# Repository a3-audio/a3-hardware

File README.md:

# SPDX-FileCopyrightText: 2017 Free Software Foundation Europe e.V. <https://fsfe.org>
#
# SPDX-License-Identifier: CERN-OHL-S-2.0

Copyright A3 Audio UG (haftungsbeschränkt) 2022.

This source describes Open Hardware and is licensed under the
CERN-OHL-S v2. You may redistribute and modify this source and make
products using it under the terms of the CERN-OHL-S v2
(https://cern-ohl.web.cern.ch).

This source is distributed WITHOUT ANY EXPRESS OR IMPLIED WARRANTY,
INCLUDING OF MERCHANTABILITY, SATISFACTORY QUALITY AND FITNESS FOR A
PARTICULAR PURPOSE. Please see the CERN-OHL-S v2 for applicable
conditions.

Source location: https://github.com/a3-audio/a3-hardware

As per CERN-OHL-S v2 section 4, should You produce hardware based on
this source, You must where practicable maintain the Source Location
visible on the external case of all products you
make using this source.

You may use "reuse" to check license validation:
https://reuse.readthedocs.io/en/stable/readme.html

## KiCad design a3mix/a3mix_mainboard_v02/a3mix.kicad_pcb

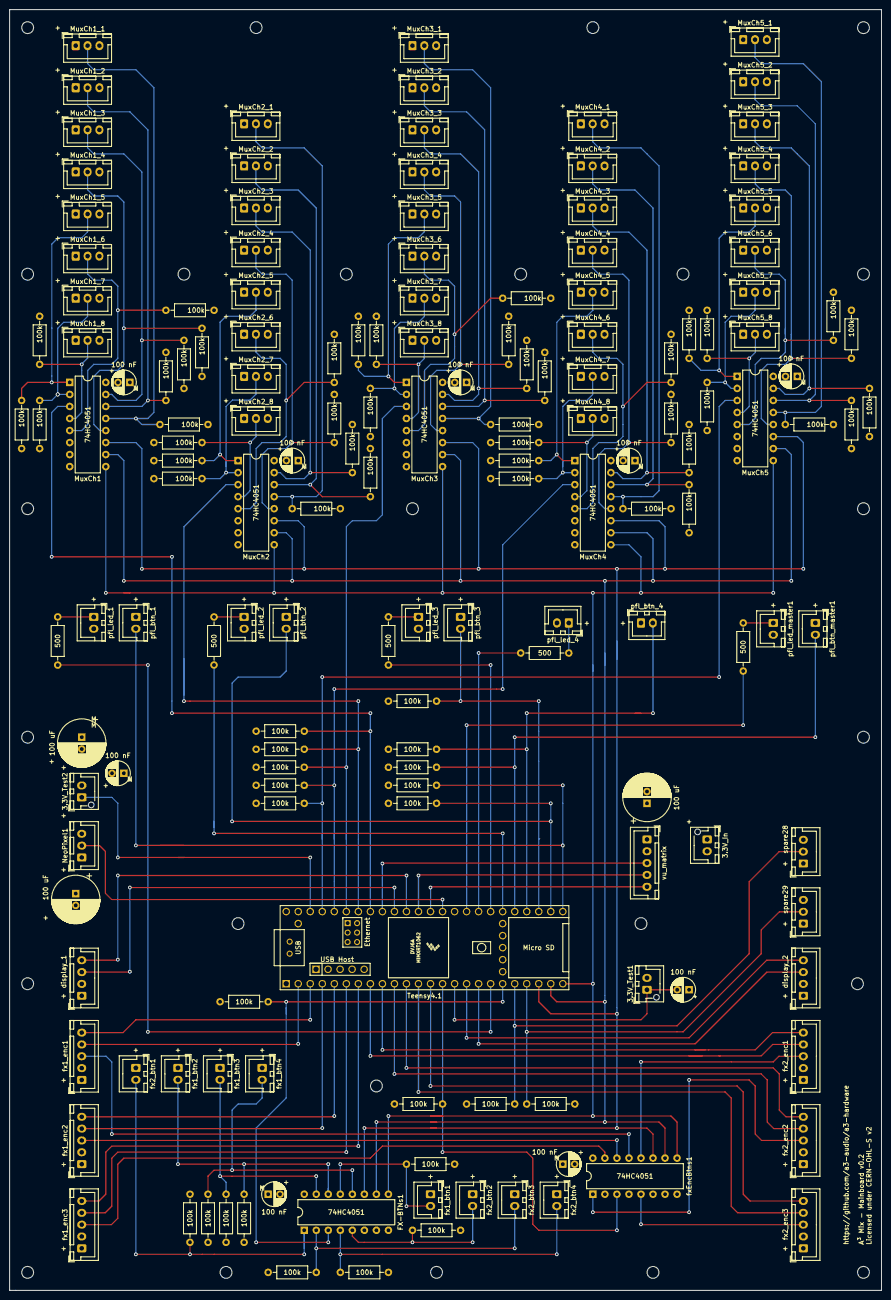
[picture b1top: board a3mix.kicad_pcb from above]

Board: 4 copper layers, 184.2 x 270.5 mm, 160 parts (0 on the bottom side), 105 nets.

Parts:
3.3V_In, 3.3V_Test1, 3.3V_Test2: Conn_01x02; JST_XH_B2B-XH-AM_1x02_P2.50mm_Vertical
C1, C2, C7: 100 uF; CP_Radial_D10.0mm_P2.50mm
C3, C4, C5, C6, C8, C9, C10, C11, C12: 100 nF; CP_Radial_D5.0mm_P2.50mm
FX-BTNs1: 74HC4051; DIP-16_W7.62mm
MuxCh1, MuxCh2, MuxCh3, MuxCh4, MuxCh5: 74HC4051; DIP-16_W7.62mm
MuxCh1_1, MuxCh1_2, MuxCh1_3, MuxCh1_4, MuxCh1_5, MuxCh1_6, MuxCh1_7, MuxCh1_8, MuxCh2_1, MuxCh2_2, MuxCh2_3, MuxCh2_4, MuxCh2_5, MuxCh2_6, MuxCh2_7, MuxCh2_8, MuxCh3_1, MuxCh3_2, MuxCh3_3, MuxCh3_4, MuxCh3_5, MuxCh3_6, MuxCh3_7, MuxCh3_8, MuxCh4_1, MuxCh4_2, MuxCh4_3, MuxCh4_4, MuxCh4_5, MuxCh4_6, MuxCh4_7, MuxCh4_8, MuxCh5_1, MuxCh5_2, MuxCh5_3, MuxCh5_4, MuxCh5_5, MuxCh5_6, MuxCh5_7, MuxCh5_8: Conn_01x03; JST_XH_B3B-XH-A_1x03_P2.50mm_Vertical
NeoPixel1: Conn_01x03; JST_XH_B3B-XH-A_1x03_P2.50mm_Vertical
R1, R2, R3, R4, R5, R6, R7, R8, R9, R10, R11, R12, R13, R14, R15, R16, R17, R19, R20, R21, R22, R23, R24, R25, R26, R27, R28, R29, R34, R35, R36, R37, R38, R39, R40, R41, R42, R43, R44, R45, R46, R47, R48, R49, R50, R51, R52, R53, R54, R55, R56, R57, R58, R59, R60, R61, R62, R63, R64, R65, R66, R67: 100k; R_Axial_DIN0207_L6.3mm_D2.5mm_P10.16mm_Horizontal
R18, R30, R31, R32, R33: 500; R_Axial_DIN0207_L6.3mm_D2.5mm_P10.16mm_Horizontal
U5: Teensy4.1; Teensy41
display_1, display_2: Conn_01x04; JST_XH_B4B-XH-A_1x04_P2.50mm_Vertical
fx1_btn1, fx1_btn2, fx1_btn3, fx1_btn4, fx2_btn1, fx2_btn2, fx2_btn3, fx2_btn4: Conn_01x02; JST_XH_B2B-XH-A_1x02_P2.50mm_Vertical
fx1_enc1, fx1_enc2, fx1_enc3, fx2_enc1, fx2_enc2, fx2_enc3: Conn_01x05; JST_XH_B5B-XH-A_1x05_P2.50mm_Vertical
fxEncBtns1: 74HC4051; DIP-16_W7.62mm
pfl_btn_1, pfl_btn_2, pfl_btn_3, pfl_btn_4: Conn_01x02; JST_XH_B2B-XH-A_1x02_P2.50mm_Vertical
pfl_btn_master1: Conn_01x02; JST_XH_B2B-XH-A_1x02_P2.50mm_Vertical
pfl_led_1, pfl_led_2, pfl_led_3, pfl_led_4: Conn_01x02; JST_XH_B2B-XH-A_1x02_P2.50mm_Vertical
pfl_led_master1: Conn_01x02; JST_XH_B2B-XH-A_1x02_P2.50mm_Vertical
spare28, spare29: Conn_01x03; JST_XH_B3B-XH-A_1x03_P2.50mm_Vertical
vu_matrix: MAX7219 led matrix vu; JST_XH_B5B-XH-A_1x05_P2.50mm_Vertical

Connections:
+3V3: 3.3V_In.1, 3.3V_Test1.2, 3.3V_Test2.2, C1.1, C2.1, C4.2, C5.2, C6.2, C7.2, C8.2, C9.2, C10.2, C11.2, C12.2, FX-BTNs1.16, MuxCh1.16, MuxCh1_1.1, MuxCh1_2.1, MuxCh1_3.1, MuxCh1_4.1, MuxCh1_5.1, MuxCh1_6.1, MuxCh1_7.1, MuxCh1_8.1, MuxCh2.16, MuxCh2_1.1, MuxCh2_2.1, MuxCh2_3.1, MuxCh2_4.1, MuxCh2_5.1, MuxCh2_6.1, MuxCh2_7.1, MuxCh2_8.1, MuxCh3.16, MuxCh3_1.1, MuxCh3_2.1, MuxCh3_3.1, MuxCh3_4.1, MuxCh3_5.1, MuxCh3_6.1, MuxCh3_7.1, MuxCh3_8.1, MuxCh4.16, MuxCh4_1.1, MuxCh4_2.1, MuxCh4_3.1, MuxCh4_4.1, MuxCh4_5.1, MuxCh4_6.1, MuxCh4_7.1, MuxCh4_8.1, MuxCh5.16, MuxCh5_1.1, MuxCh5_2.1, MuxCh5_3.1, MuxCh5_4.1, MuxCh5_5.1, MuxCh5_6.1, MuxCh5_7.1, MuxCh5_8.1, NeoPixel1.1, display_1.1, display_2.1, fx1_btn1.1, fx1_btn2.1, fx1_btn3.1, fx1_btn4.1, fx1_enc1.1, fx1_enc2.1, fx1_enc3.1, fx2_btn1.1, fx2_btn2.1, fx2_btn3.1, fx2_btn4.1, fx2_enc1.1, fx2_enc2.1, fx2_enc3.1, fxEncBtns1.16, pfl_btn_1.1, pfl_btn_2.1, pfl_btn_3.1, pfl_btn_4.1, pfl_btn_master1.1, spare28.1, spare29.1, vu_matrix.1
GND: 3.3V_In.2, C1.2, C2.2, C3.1, C4.1, C5.1, C6.1, C7.1, C8.1, C9.1, C10.1, C11.1, C12.1, FX-BTNs1.6, FX-BTNs1.7, FX-BTNs1.8, MuxCh1.6, MuxCh1.7, MuxCh1.8, MuxCh1_1.3, MuxCh1_2.3, MuxCh1_3.3, MuxCh1_4.3, MuxCh1_5.3, MuxCh1_6.3, MuxCh1_7.3, MuxCh1_8.3, MuxCh2.6, MuxCh2.7, MuxCh2.8, MuxCh2_1.3, MuxCh2_2.3, MuxCh2_3.3, MuxCh2_4.3, MuxCh2_5.3, MuxCh2_6.3, MuxCh2_7.3, MuxCh2_8.3, MuxCh3.6, MuxCh3.7, MuxCh3.8, MuxCh3_1.3, MuxCh3_2.3, MuxCh3_3.3, MuxCh3_4.3, MuxCh3_5.3, MuxCh3_6.3, MuxCh3_7.3, MuxCh3_8.3, MuxCh4.6, MuxCh4.7, MuxCh4.8, MuxCh4_1.3, MuxCh4_2.3, MuxCh4_3.3, MuxCh4_4.3, MuxCh4_5.3, MuxCh4_6.3, MuxCh4_7.3, MuxCh4_8.3, MuxCh5.6, MuxCh5.7, MuxCh5.8, MuxCh5_1.3, MuxCh5_2.3, MuxCh5_3.3, MuxCh5_4.3, MuxCh5_5.3, MuxCh5_6.3, MuxCh5_7.3, MuxCh5_8.3, NeoPixel1.3, R1.2, R2.2, R3.2, R4.2, R5.2, R6.2, R7.2, R8.2, R9.2, R10.2, R11.2, R12.2, R13.2, R14.2, R15.2, R16.2, R17.2, R19.2, R20.2, R21.2, R22.2, R23.2, R24.2, R25.2, R26.2, R27.2, R28.2, R29.2, R34.2, R35.2, R36.2, R37.2, R38.2, R39.2, R40.2, R41.2, R42.2, R43.2, R44.2, R45.2, R46.2, R47.2, R48.2, R49.2, R50.2, R51.2, R52.2, R53.2, R54.2, R55.2, R56.2, R57.2, R58.2, R59.2, R60.2, R61.2, R62.2, R63.2, R64.2, R65.2, R66.2, R67.2, U5.1, U5.34, U5.47, display_1.2, display_2.2, fx1_enc1.2, fx1_enc2.2, fx1_enc3.2, fx2_enc1.2, fx2_enc2.2, fx2_enc3.2, fxEncBtns1.6, fxEncBtns1.7, fxEncBtns1.8, pfl_led_1.2, pfl_led_2.2, pfl_led_3.2, pfl_led_4.2, pfl_led_master1.2, spare28.3, spare29.3, vu_matrix.2
unnamed: 3.3V_Test1.1, C3.2, U5.15
unnamed: 3.3V_Test2.1, U5.46
unnamed: FX-BTNs1.1, R5.1, fx2_btn1.2
unnamed: FX-BTNs1.2, R7.1, fx2_btn3.2
unnamed: FX-BTNs1.4, R8.1, fx2_btn4.2
unnamed: FX-BTNs1.5, R6.1, fx2_btn2.2
unnamed: FX-BTNs1.12, R4.1, fx1_btn4.2
unnamed: FX-BTNs1.13, R1.1, fx1_btn1.2
unnamed: FX-BTNs1.14, R2.1, fx1_btn2.2
unnamed: FX-BTNs1.15, R3.1, fx1_btn3.2
unnamed: MuxCh1.1, MuxCh1_5.2, R13.1
unnamed: MuxCh1.2, MuxCh1_7.2, R15.1
unnamed: MuxCh1.4, MuxCh1_8.2, R16.1
unnamed: MuxCh1.5, MuxCh1_6.2, R14.1
unnamed: MuxCh1.12, MuxCh1_4.2, R12.1
unnamed: MuxCh1.13, MuxCh1_1.2, R9.1
unnamed: MuxCh1.14, MuxCh1_2.2, R10.1
unnamed: MuxCh1.15, MuxCh1_3.2, R11.1
unnamed: MuxCh2.13, MuxCh2_1.2, R22.1
unnamed: MuxCh2.14, MuxCh2_2.2, R23.1
unnamed: MuxCh2.15, MuxCh2_3.2, R24.1
unnamed: MuxCh2.12, MuxCh2_4.2, R25.1
unnamed: MuxCh2.1, MuxCh2_5.2, R26.1
unnamed: MuxCh2.5, MuxCh2_6.2, R27.1
unnamed: MuxCh2.2, MuxCh2_7.2, R28.1
unnamed: MuxCh2.4, MuxCh2_8.2, R29.1
unnamed: MuxCh3.13, MuxCh3_1.2, R44.1
unnamed: MuxCh3.14, MuxCh3_2.2, R45.1
unnamed: MuxCh3.15, MuxCh3_3.2, R46.1
unnamed: MuxCh3.12, MuxCh3_4.2, R47.1
unnamed: MuxCh3.1, MuxCh3_5.2, R48.1
unnamed: MuxCh3.5, MuxCh3_6.2, R49.1
unnamed: MuxCh3.2, MuxCh3_7.2, R50.1
unnamed: MuxCh3.4, MuxCh3_8.2, R51.1
unnamed: MuxCh4.13, MuxCh4_1.2, R52.1
unnamed: MuxCh4.14, MuxCh4_2.2, R53.1
unnamed: MuxCh4.15, MuxCh4_3.2, R54.1
unnamed: MuxCh4.12, MuxCh4_4.2, R55.1
unnamed: MuxCh4.1, MuxCh4_5.2, R56.1
unnamed: MuxCh4.5, MuxCh4_6.2, R57.1
unnamed: MuxCh4.2, MuxCh4_7.2, R58.1
unnamed: MuxCh4.4, MuxCh4_8.2, R59.1
unnamed: MuxCh5.13, MuxCh5_1.2, R60.1
unnamed: MuxCh5.14, MuxCh5_2.2, R61.1
unnamed: MuxCh5.15, MuxCh5_3.2, R62.1
unnamed: MuxCh5.12, MuxCh5_4.2, R63.1
unnamed: MuxCh5.1, MuxCh5_5.2, R64.1
unnamed: MuxCh5.5, MuxCh5_6.2, R65.1
unnamed: MuxCh5.2, MuxCh5_7.2, R66.1
unnamed: MuxCh5.4, MuxCh5_8.2, R67.1
unnamed: R18.1, U5.18
unnamed: R30.2, U5.33
unnamed: R31.2, U5.32
unnamed: R32.2, U5.31
unnamed: R33.2, U5.30
unnamed: fx1_enc1.3, fxEncBtns1.13
unnamed: fx1_enc2.3, fxEncBtns1.14
unnamed: fx1_enc3.3, fxEncBtns1.15
unnamed: fx2_enc1.3, fxEncBtns1.12
unnamed: fx2_enc2.3, fxEncBtns1.1
unnamed: fx2_enc3.3, fxEncBtns1.5
display_scl1: U5.38, display_1.4
display_scl2: U5.16, display_2.4
display_sda1: U5.39, display_1.3
display_sda2: U5.17, display_2.3
mux_ch1: MuxCh1.3, R38.1, U5.41
mux_ch2: MuxCh2.3, R37.1, U5.42
mux_ch3: MuxCh3.3, R36.1, U5.43
mux_ch4: MuxCh4.3, R35.1, U5.44
mux_encBtn_fx: R17.1, U5.14, fxEncBtns1.3
mux_master: MuxCh5.3, R34.1, U5.45
mux_selBtn_fx: FX-BTNs1.3, R19.1, U5.19
neopixel: NeoPixel1.2, U5.35
pfl_btn_ch1: R43.1, U5.25, pfl_btn_1.2
pfl_btn_ch2: R42.1, U5.26, pfl_btn_2.2
pfl_btn_ch3: R41.1, U5.27, pfl_btn_3.2
pfl_btn_ch4: R40.1, U5.28, pfl_btn_4.2
pfl_btn_master: R39.1, U5.29, pfl_btn_master1.2
pfl_led_ch1: R18.2, pfl_led_1.1
pfl_led_ch2: R33.1, pfl_led_2.1
pfl_led_ch3: R32.1, pfl_led_3.1
pfl_led_ch4: R31.1, pfl_led_4.1
pfl_led_master: R30.1, pfl_led_master1.1
pin28: R20.1, U5.20, spare28.2
pin29: R21.1, U5.21, spare29.2
rEnc0_DT: U5.2, fx1_enc1.4
rEnc0_clk: U5.3, fx1_enc1.5
rEnc1_DT: U5.4, fx1_enc2.4
rEnc1_clk: U5.5, fx1_enc2.5
rEnc2_DT: U5.6, fx1_enc3.4
rEnc2_clk: U5.7, fx1_enc3.5
rEnc3_DT: U5.8, fx2_enc1.4
rEnc3_clk: U5.9, fx2_enc1.5
rEnc4_DT: U5.10, fx2_enc2.4
rEnc4_clk: U5.11, fx2_enc2.5
rEnc5_DT: U5.12, fx2_enc3.4
rEnc5_clk: U5.13, fx2_enc3.5
s0: FX-BTNs1.11, MuxCh1.11, MuxCh2.11, MuxCh3.11, MuxCh4.11, MuxCh5.11, U5.22, fxEncBtns1.11
s1: FX-BTNs1.10, MuxCh1.10, MuxCh2.10, MuxCh3.10, MuxCh4.10, MuxCh5.10, U5.23, fxEncBtns1.10
s2: FX-BTNs1.9, MuxCh1.9, MuxCh2.9, MuxCh3.9, MuxCh4.9, MuxCh5.9, U5.24, fxEncBtns1.9
vu_clk: U5.36, vu_matrix.5
vu_cs: U5.37, vu_matrix.4
vu_din: U5.40, vu_matrix.3

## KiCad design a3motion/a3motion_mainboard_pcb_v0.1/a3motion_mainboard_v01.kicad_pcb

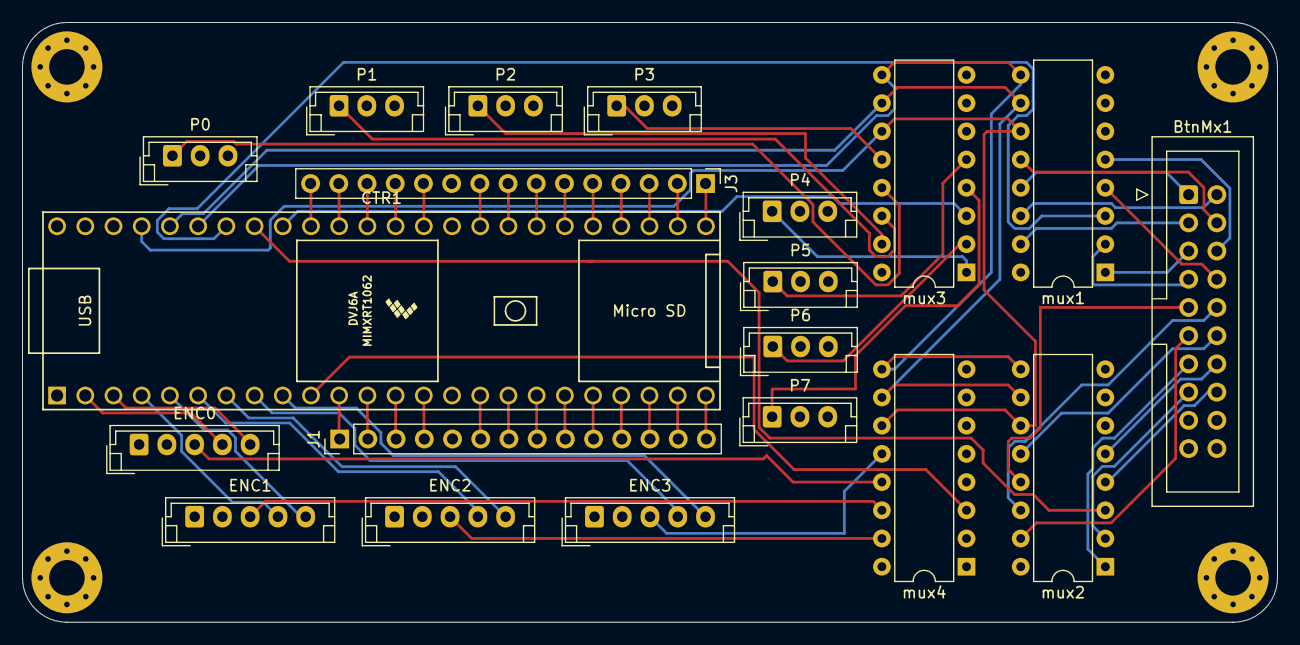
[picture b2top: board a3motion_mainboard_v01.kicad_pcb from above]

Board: 4 copper layers, 113.0 x 54.0 mm, 20 parts (0 on the bottom side), 72 nets.

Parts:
BtnMx1: Conn_02x09_Counter_Clockwise; IDC-Header_2x10_P2.54mm_Vertical
CTR1: Teensy4.1; Teensy41_my
ENC0, ENC1, ENC2, ENC3: Conn_01x05; JST_EH_B5B-EH-A_1x05_P2.50mm_Vertical
J1: Conn_01x14_Male; PinHeader_1x14_P2.54mm_Vertical
J3: Conn_01x15_Male; PinHeader_1x15_P2.54mm_Vertical
P0, P1, P2, P3, P4, P5, P6, P7: Conn_01x03; JST_EH_B3B-EH-A_1x03_P2.50mm_Vertical
mux1, mux2, mux3, mux4: 74HC4051; DIP-16_W7.62mm

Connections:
+3V3: BtnMx1.20, CTR1.15, CTR1.46, ENC0.2, ENC1.2, ENC2.2, ENC3.2, J1.5, P0.3, P1.3, P2.3, P3.3, P4.3, P5.3, P6.3, P7.3, mux1.16, mux2.16, mux3.16, mux4.16
GND: BtnMx1.19, CTR1.1, CTR1.34, CTR1.47, ENC0.1, ENC1.1, ENC2.1, ENC3.1, J3.10, P0.2, P1.2, P2.2, P3.2, P4.2, P5.2, P6.2, P7.2, mux1.6, mux1.7, mux1.8, mux2.6, mux2.7, mux2.8, mux3.6, mux3.7, mux3.8, mux4.6, mux4.7, mux4.8
unnamed: BtnMx1.1, mux1.13
unnamed: BtnMx1.2, mux1.14
unnamed: BtnMx1.3, mux1.15
unnamed: BtnMx1.4, mux1.12
unnamed: BtnMx1.5, mux1.1
unnamed: BtnMx1.6, mux1.5
unnamed: BtnMx1.7, mux1.2
unnamed: BtnMx1.8, mux1.4
unnamed: BtnMx1.9, mux2.13
unnamed: BtnMx1.10, mux2.14
unnamed: BtnMx1.11, mux2.15
unnamed: BtnMx1.12, mux2.12
unnamed: BtnMx1.13, mux2.1
unnamed: BtnMx1.14, mux2.5
unnamed: BtnMx1.15, mux2.2
unnamed: BtnMx1.16, mux2.4
unnamed: CTR1.11, J1.1
unnamed: CTR1.12, J1.2
unnamed: CTR1.13, J1.3
unnamed: CTR1.14, J1.4
unnamed: CTR1.16, J1.6
unnamed: CTR1.17, J1.7
unnamed: CTR1.18, J1.8
unnamed: CTR1.19, J1.9
unnamed: CTR1.20, J1.10
unnamed: CTR1.21, J1.11
unnamed: CTR1.22, J1.12
unnamed: CTR1.23, J1.13
unnamed: CTR1.24, J1.14
unnamed: CTR1.25, J3.1
unnamed: CTR1.26, J3.2
unnamed: CTR1.27, J3.3
unnamed: CTR1.28, J3.4
unnamed: CTR1.29, J3.5
unnamed: CTR1.30, J3.6
unnamed: CTR1.31, J3.7
unnamed: CTR1.32, J3.8
unnamed: CTR1.33, J3.9
unnamed: CTR1.35, J3.11
unnamed: CTR1.36, J3.12
unnamed: CTR1.37, J3.13
unnamed: CTR1.38, J3.14
unnamed: CTR1.39, J3.15
unnamed: ENC0.3, mux4.13
unnamed: ENC1.3, mux4.14
unnamed: ENC2.3, mux4.15
unnamed: ENC3.3, mux4.12
unnamed: P0.1, mux3.13
unnamed: P1.1, mux3.14
unnamed: P2.1, mux3.15
unnamed: P3.1, mux3.12
unnamed: P4.1, mux3.1
unnamed: P5.1, mux3.5
unnamed: P6.1, mux3.2
unnamed: P7.1, mux3.4
mux_btnMx1: CTR1.42, mux1.3
mux_btnMx2: CTR1.41, mux2.3
mux_btn_rEnc: CTR1.10, mux4.3
mux_porty: CTR1.40, mux3.3
rEnc0_CLK: CTR1.3, ENC0.5
rEnc0_DT: CTR1.2, ENC0.4
rEnc1_CLK: CTR1.5, ENC1.5
rEnc1_DT: CTR1.4, ENC1.4
rEnc2_CLK: CTR1.7, ENC2.5
rEnc2_DT: CTR1.6, ENC2.4
rEnc3_CLK: CTR1.9, ENC3.5
rEnc3_DT: CTR1.8, ENC3.4
s0: CTR1.45, mux1.11, mux2.11, mux3.11, mux4.11
s1: CTR1.44, mux1.10, mux2.10, mux3.10, mux4.10
s2: CTR1.43, mux1.9, mux2.9, mux3.9, mux4.9

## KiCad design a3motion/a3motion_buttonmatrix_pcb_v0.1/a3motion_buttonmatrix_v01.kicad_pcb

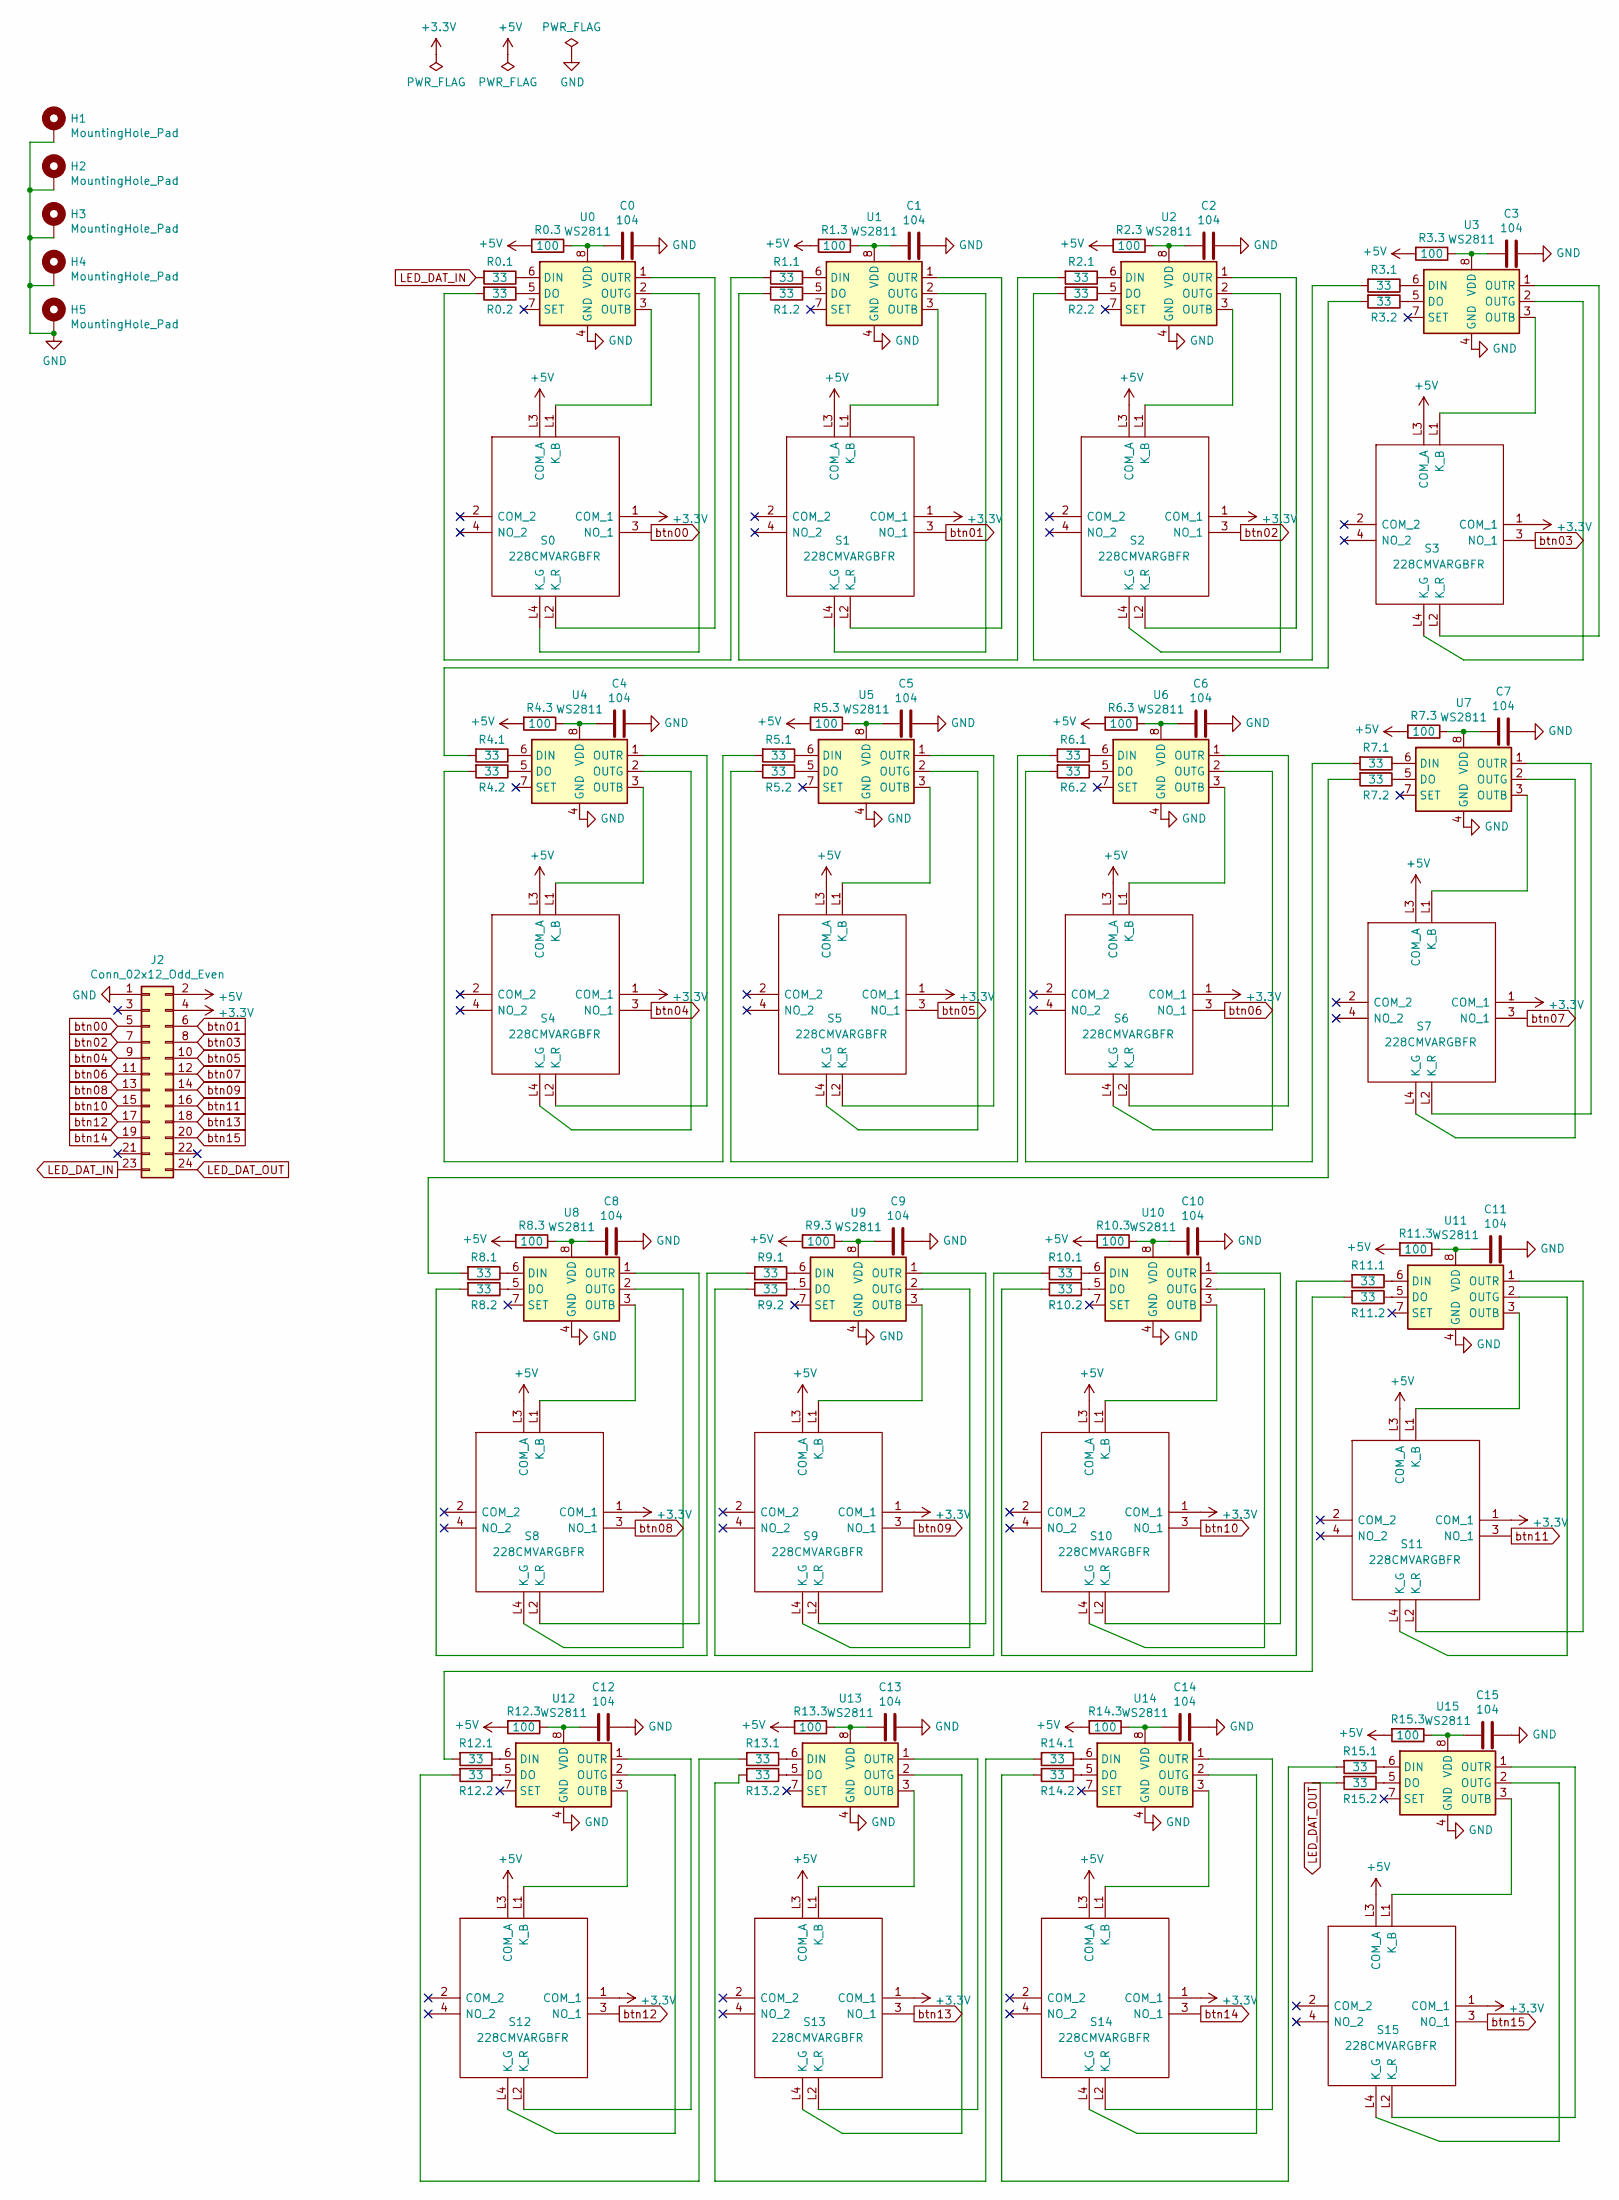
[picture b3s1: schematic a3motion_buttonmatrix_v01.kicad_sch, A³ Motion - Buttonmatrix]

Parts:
C0, C1, C2, C3, C4, C5, C6, C7, C8, C9, C10, C11, C12, C13, C14, C15: 104; C_1206_3216Metric
H1, H2, H3, H4, H5: MountingHole_Pad; MountingHole_2.7mm_Pad_Via
J2: Conn_02x12_Odd_Even; IDC-Header_2x12_P2.54mm_Vertical
R0.1, R0.2, R1.1, R1.2, R2.1, R2.2, R3.1, R3.2, R4.1, R4.2, R5.1, R5.2, R6.1, R6.2, R7.1, R7.2, R8.1, R8.2, R9.1, R9.2, R10.1, R10.2, R11.1, R11.2, R12.1, R12.2, R13.1, R13.2, R14.1, R14.2, R15.1, R15.2: 33; R_2512_6332Metric
R0.3, R1.3, R2.3, R3.3, R4.3, R5.3, R6.3, R7.3, R8.3, R9.3, R10.3, R11.3, R12.3, R13.3, R14.3, R15.3: 100; R_2512_6332Metric
S0, S1, S2, S3, S4, S5, S6, S7, S8, S9, S10, S11, S12, S13, S14, S15: 228CMVARGBFR; Mouser Part Number 774-228CMVARGBFR
U0, U1, U2, U3, U4, U5, U6, U7, U8, U9, U10, U11, U12, U13, U14, U15: WS2811; SOP-8_3.9x4.9mm_P1.27mm

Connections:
+3V3: J2.4, S0.1 (COM_1), S1.1 (COM_1), S2.1 (COM_1), S3.1 (COM_1), S4.1 (COM_1), S5.1 (COM_1), S6.1 (COM_1), S7.1 (COM_1), S8.1 (COM_1), S9.1 (COM_1), S10.1 (COM_1), S11.1 (COM_1), S12.1 (COM_1), S13.1 (COM_1), S14.1 (COM_1), S15.1 (COM_1)
+5V: J2.2, R0.3.2, R1.3.2, R2.3.2, R3.3.2, R4.3.2, R5.3.2, R6.3.2, R7.3.2, R8.3.2, R9.3.2, R10.3.2, R11.3.2, R12.3.2, R13.3.2, R14.3.2, R15.3.2, S0.L3 (COM_A), S1.L3 (COM_A), S2.L3 (COM_A), S3.L3 (COM_A), S4.L3 (COM_A), S5.L3 (COM_A), S6.L3 (COM_A), S7.L3 (COM_A), S8.L3 (COM_A), S9.L3 (COM_A), S10.L3 (COM_A), S11.L3 (COM_A), S12.L3 (COM_A), S13.L3 (COM_A), S14.L3 (COM_A), S15.L3 (COM_A)
GND: C0.2, C1.2, C2.2, C3.2, C4.2, C5.2, C6.2, C7.2, C8.2, C9.2, C10.2, C11.2, C12.2, C13.2, C14.2, C15.2, H1.1, H2.1, H3.1, H4.1, H5.1, J2.1, U0.4 (GND), U1.4 (GND), U2.4 (GND), U3.4 (GND), U4.4 (GND), U5.4 (GND), U6.4 (GND), U7.4 (GND), U8.4 (GND), U9.4 (GND), U10.4 (GND), U11.4 (GND), U12.4 (GND), U13.4 (GND), U14.4 (GND), U15.4 (GND)
LED_DAT_IN: J2.23, R0.1.2
LED_DAT_OUT: J2.24, R15.2.2
unnamed: C0.1, R0.3.1, U0.8 (VDD)
unnamed: C1.1, R1.3.1, U1.8 (VDD)
unnamed: C2.1, R2.3.1, U2.8 (VDD)
unnamed: C3.1, R3.3.1, U3.8 (VDD)
unnamed: C4.1, R4.3.1, U4.8 (VDD)
unnamed: C5.1, R5.3.1, U5.8 (VDD)
unnamed: C6.1, R6.3.1, U6.8 (VDD)
unnamed: C7.1, R7.3.1, U7.8 (VDD)
unnamed: C8.1, R8.3.1, U8.8 (VDD)
unnamed: C9.1, R9.3.1, U9.8 (VDD)
unnamed: C10.1, R10.3.1, U10.8 (VDD)
unnamed: C11.1, R11.3.1, U11.8 (VDD)
unnamed: C12.1, R12.3.1, U12.8 (VDD)
unnamed: C13.1, R13.3.1, U13.8 (VDD)
unnamed: C14.1, R14.3.1, U14.8 (VDD)
unnamed: C15.1, R15.3.1, U15.8 (VDD)
unnamed: R0.1.1, U0.6 (DIN)
unnamed: R0.2.1, U0.5 (DO)
unnamed: R0.2.2, R1.1.2
unnamed: R1.1.1, U1.6 (DIN)
unnamed: R1.2.1, U1.5 (DO)
unnamed: R1.2.2, R2.1.2
unnamed: R2.1.1, U2.6 (DIN)
unnamed: R2.2.1, U2.5 (DO)
unnamed: R2.2.2, R3.1.2
unnamed: R3.1.1, U3.6 (DIN)
unnamed: R3.2.1, U3.5 (DO)
unnamed: R3.2.2, R4.1.2
unnamed: R4.1.1, U4.6 (DIN)
unnamed: R4.2.1, U4.5 (DO)
unnamed: R4.2.2, R5.1.2
unnamed: R5.1.1, U5.6 (DIN)
unnamed: R5.2.1, U5.5 (DO)
unnamed: R5.2.2, R6.1.2
unnamed: R6.1.1, U6.6 (DIN)
unnamed: R6.2.1, U6.5 (DO)
unnamed: R6.2.2, R7.1.2
unnamed: R7.1.1, U7.6 (DIN)
unnamed: R7.2.1, U7.5 (DO)
unnamed: R7.2.2, R8.1.2
unnamed: R8.1.1, U8.6 (DIN)
unnamed: R8.2.1, U8.5 (DO)
unnamed: R8.2.2, R9.1.2
unnamed: R9.1.1, U9.6 (DIN)
unnamed: R9.2.1, U9.5 (DO)
unnamed: R10.1.1, U10.6 (DIN)
unnamed: R9.2.2, R10.1.2
unnamed: R10.2.1, U10.5 (DO)
unnamed: R10.2.2, R11.1.2
unnamed: R11.1.1, U11.6 (DIN)
unnamed: R11.2.1, U11.5 (DO)
unnamed: R11.2.2, R12.1.2
unnamed: R12.1.1, U12.6 (DIN)
unnamed: R12.2.1, U12.5 (DO)
unnamed: R12.2.2, R13.1.2
unnamed: R13.1.1, U13.6 (DIN)
unnamed: R13.2.1, U13.5 (DO)
unnamed: R13.2.2, R14.1.2
unnamed: R14.1.1, U14.6 (DIN)
unnamed: R14.2.1, U14.5 (DO)
unnamed: R14.2.2, R15.1.2
unnamed: R15.1.1, U15.6 (DIN)
unnamed: R15.2.1, U15.5 (DO)
unnamed: S0.L1 (K_B), U0.3 (OUTB)
unnamed: S0.L2 (K_R), U0.1 (OUTR)
unnamed: S0.L4 (K_G), U0.2 (OUTG)
unnamed: S1.L1 (K_B), U1.3 (OUTB)
unnamed: S1.L2 (K_R), U1.1 (OUTR)
unnamed: S1.L4 (K_G), U1.2 (OUTG)
unnamed: S2.L1 (K_B), U2.3 (OUTB)
unnamed: S2.L2 (K_R), U2.1 (OUTR)
unnamed: S2.L4 (K_G), U2.2 (OUTG)
unnamed: S3.L1 (K_B), U3.3 (OUTB)
unnamed: S3.L2 (K_R), U3.1 (OUTR)
unnamed: S3.L4 (K_G), U3.2 (OUTG)
unnamed: S4.L1 (K_B), U4.3 (OUTB)
unnamed: S4.L2 (K_R), U4.1 (OUTR)
unnamed: S4.L4 (K_G), U4.2 (OUTG)
unnamed: S5.L1 (K_B), U5.3 (OUTB)
unnamed: S5.L2 (K_R), U5.1 (OUTR)
unnamed: S5.L4 (K_G), U5.2 (OUTG)
unnamed: S6.L1 (K_B), U6.3 (OUTB)
unnamed: S6.L2 (K_R), U6.1 (OUTR)
unnamed: S6.L4 (K_G), U6.2 (OUTG)
unnamed: S7.L1 (K_B), U7.3 (OUTB)
unnamed: S7.L2 (K_R), U7.1 (OUTR)
unnamed: S7.L4 (K_G), U7.2 (OUTG)
unnamed: S8.L1 (K_B), U8.3 (OUTB)
unnamed: S8.L2 (K_R), U8.1 (OUTR)
unnamed: S8.L4 (K_G), U8.2 (OUTG)
unnamed: S9.L1 (K_B), U9.3 (OUTB)
unnamed: S9.L2 (K_R), U9.1 (OUTR)
unnamed: S9.L4 (K_G), U9.2 (OUTG)
unnamed: S10.L1 (K_B), U10.3 (OUTB)
unnamed: S10.L2 (K_R), U10.1 (OUTR)
unnamed: S10.L4 (K_G), U10.2 (OUTG)
unnamed: S11.L1 (K_B), U11.3 (OUTB)
unnamed: S11.L2 (K_R), U11.1 (OUTR)
unnamed: S11.L4 (K_G), U11.2 (OUTG)
unnamed: S12.L1 (K_B), U12.3 (OUTB)
unnamed: S12.L2 (K_R), U12.1 (OUTR)
unnamed: S12.L4 (K_G), U12.2 (OUTG)
unnamed: S13.L1 (K_B), U13.3 (OUTB)
unnamed: S13.L2 (K_R), U13.1 (OUTR)
unnamed: S13.L4 (K_G), U13.2 (OUTG)
unnamed: S14.L1 (K_B), U14.3 (OUTB)
unnamed: S14.L2 (K_R), U14.1 (OUTR)
unnamed: S14.L4 (K_G), U14.2 (OUTG)
unnamed: S15.L1 (K_B), U15.3 (OUTB)
unnamed: S15.L2 (K_R), U15.1 (OUTR)
unnamed: S15.L4 (K_G), U15.2 (OUTG)
btn00: J2.5, S0.3 (NO_1)
btn01: J2.6, S1.3 (NO_1)
btn02: J2.7, S2.3 (NO_1)
btn03: J2.8, S3.3 (NO_1)
btn04: J2.9, S4.3 (NO_1)
btn05: J2.10, S5.3 (NO_1)
btn06: J2.11, S6.3 (NO_1)
btn07: J2.12, S7.3 (NO_1)
btn08: J2.13, S8.3 (NO_1)
btn09: J2.14, S9.3 (NO_1)
btn10: J2.15, S10.3 (NO_1)
btn11: J2.16, S11.3 (NO_1)
btn12: J2.17, S12.3 (NO_1)
btn13: J2.18, S13.3 (NO_1)
btn14: J2.19, S14.3 (NO_1)
btn15: J2.20, S15.3 (NO_1)

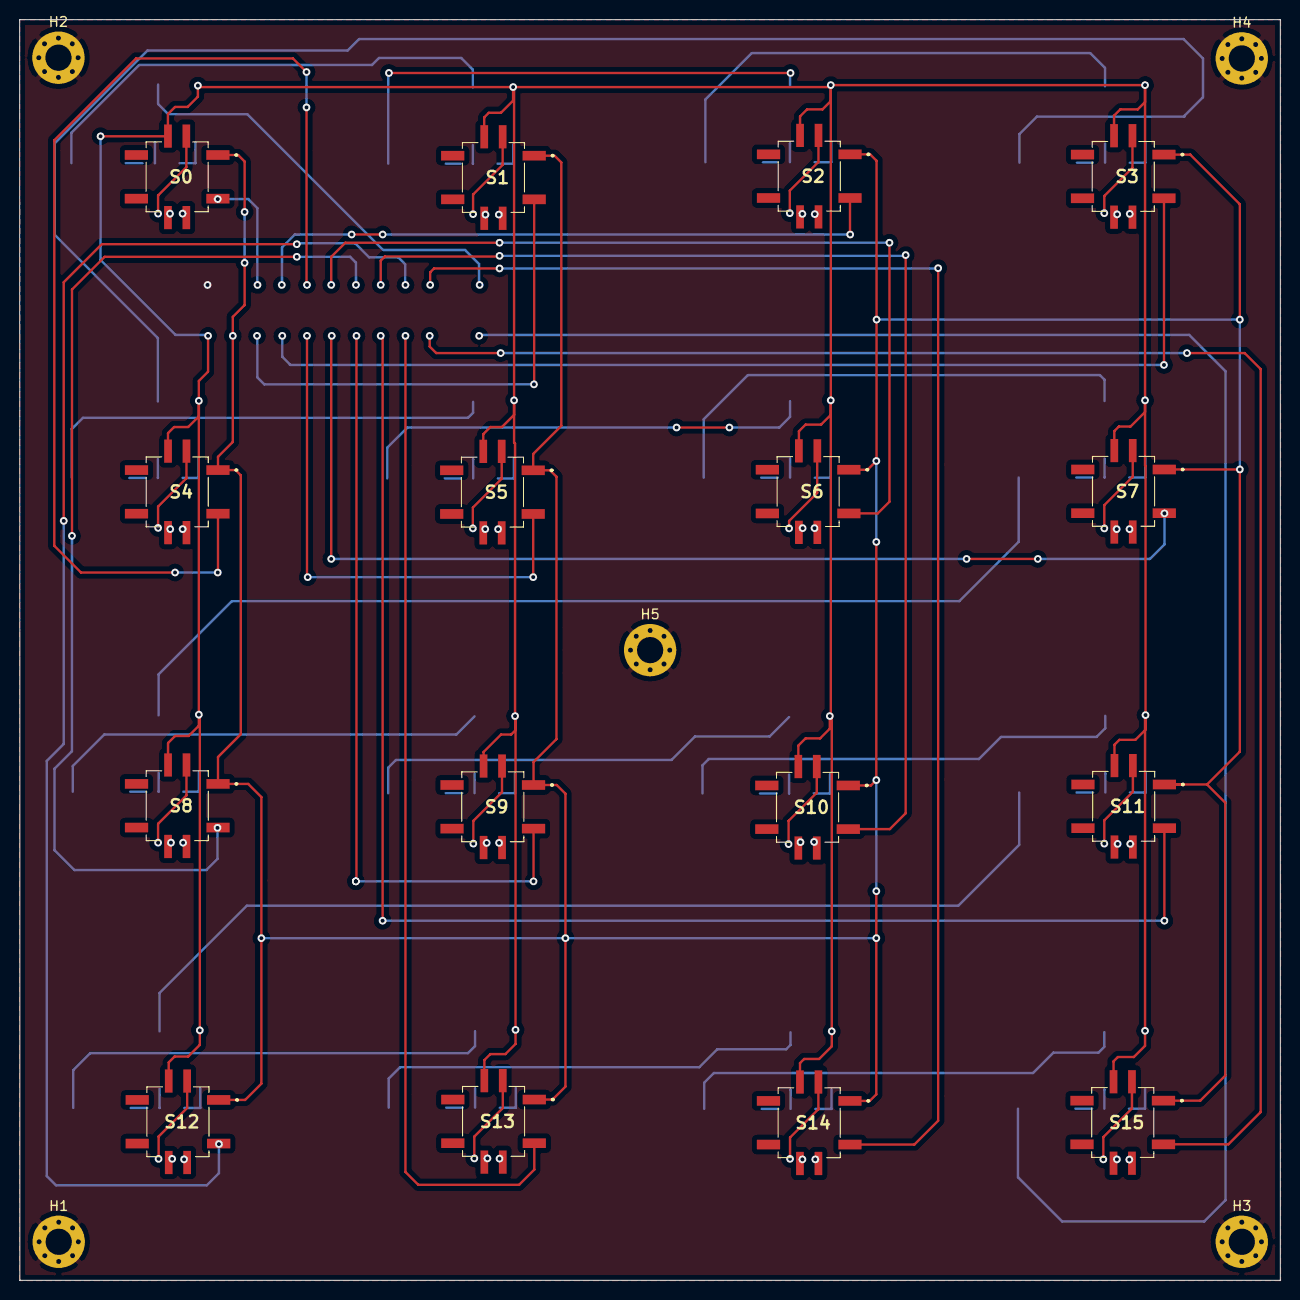
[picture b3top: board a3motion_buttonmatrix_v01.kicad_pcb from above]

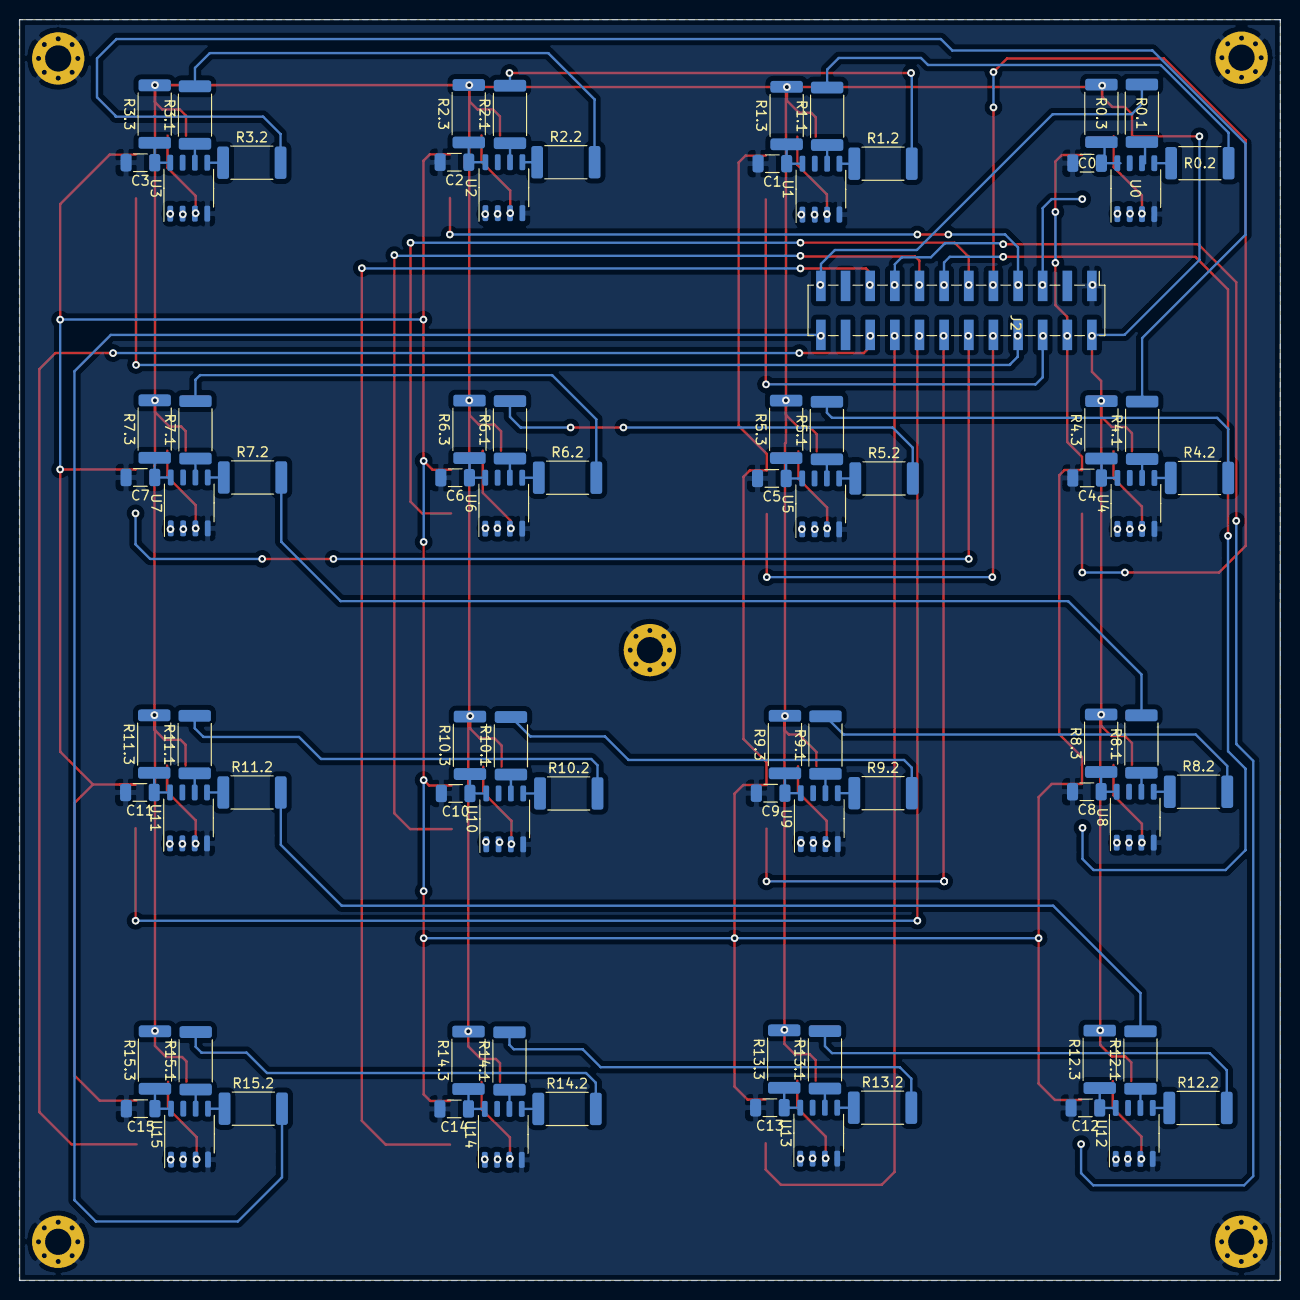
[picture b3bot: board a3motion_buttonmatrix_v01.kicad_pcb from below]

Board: 2 copper layers, 130.0 x 130.0 mm, 102 parts (81 on the bottom side), 132 nets.

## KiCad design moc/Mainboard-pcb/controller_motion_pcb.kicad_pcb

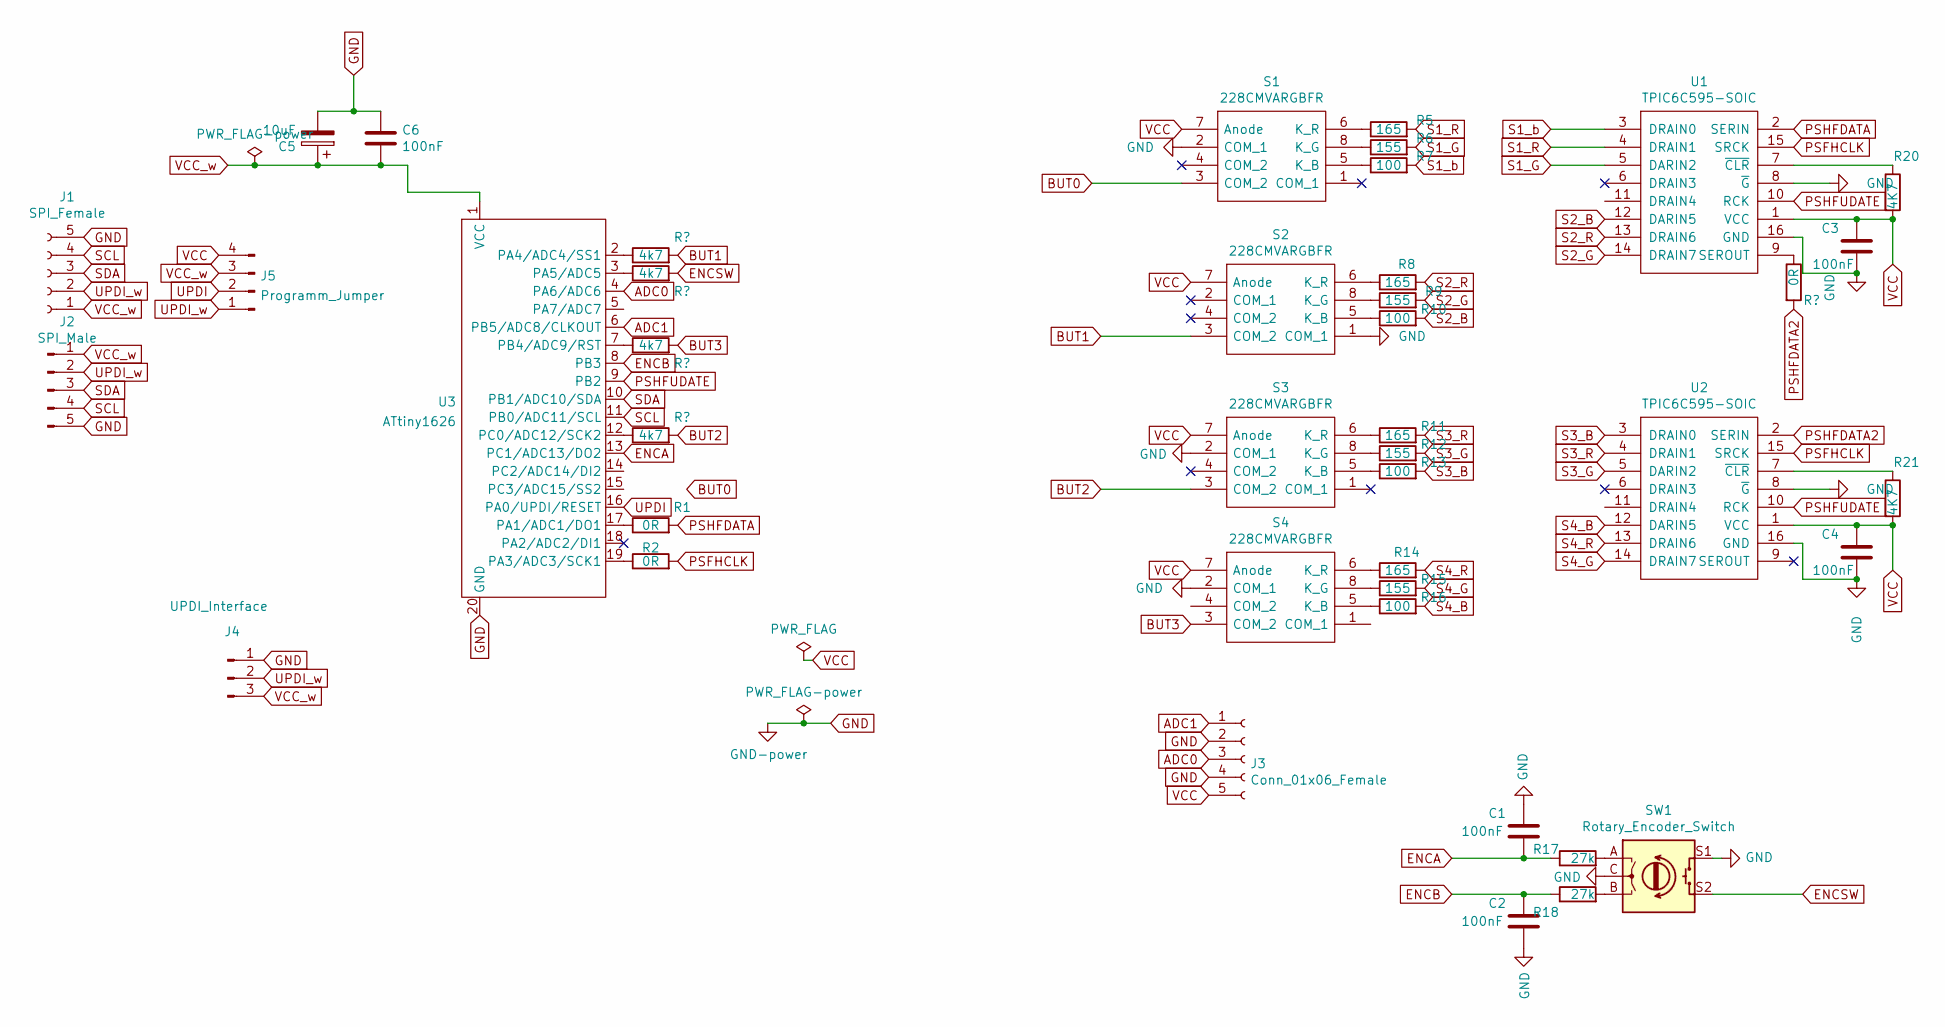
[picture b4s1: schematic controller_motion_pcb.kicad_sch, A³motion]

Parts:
C1, C2, C3, C4, C6: 100nF; C_1206_3216Metric_Pad1.33x1.80mm_HandSolder
C5: 10uF; CP_Radial_D4.0mm_P1.50mm
J1: SPI_Female; PinSocket_1x05_P2.54mm_Horizontal
J2: SPI_Male; PinHeader_1x05_P2.54mm_Horizontal
J3: Conn_01x06_Female; JST_PH_B5B-PH-K_1x05_P2.00mm_Vertical
J4: UPDI_Interface; PinHeader_1x03_P2.54mm_Vertical
J5: Programm_Jumper; PinHeader_2x02_P2.54mm_Vertical
R1, R2: 0R
R5, R8, R11, R14: 165; R_1206_3216Metric_Pad1.30x1.75mm_HandSolder
R6, R9, R12, R15: 155; R_1206_3216Metric_Pad1.30x1.75mm_HandSolder
R7, R10, R13, R16: 100; R_1206_3216Metric_Pad1.30x1.75mm_HandSolder
R17, R18: 27k; R_1206_3216Metric_Pad1.30x1.75mm_HandSolder
R20, R21: 4K7; R_1206_3216Metric_Pad1.30x1.75mm_HandSolder
S1, S2, S3, S4: 228CMVARGBFR; Mouser Part Number 774-228CMVARGBFR
SW1: Rotary_Encoder_Switch; PEC11R4230KS0024
U1, U2: TPIC6C595-SOIC; SOIC-16_3.9x9.9mm_P1.27mm
U3: ATtiny1626; attiny1626

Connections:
ADC0: J3.3, U3.4 (PA6/ADC6)
ADC1: J3.1, U3.6 (PB5/ADC8/CLKOUT)
BUT0: S1.3 (COM_2), U3.15 (PC3/ADC15/SS2)
BUT1: S2.3 (COM_2), U3.2 (PA4/ADC4/SS1)
BUT2: S3.3 (COM_2), U3.12 (PC0/ADC12/SCK2)
BUT3: S4.3 (COM_2), U3.7 (PB4/ADC9/RST)
ENCA: C1.2, R17.1, U3.13 (PC1/ADC13/DO2)
ENCB: C2.1, R18.1, U3.8 (PB3)
ENCSW: SW1.S2, U3.3 (PA5/ADC5)
GND: C1.1, C2.2, C3.2, C4.2, C5.2, C6.1, J1.5, J2.5, J3.2, J3.4, J4.1, S1.2 (COM_1), S2.1 (COM_1), S3.2 (COM_1), S4.2 (COM_1), SW1.C, SW1.S1, U1.8 (~G), U1.16 (GND), U2.8 (~G), U2.16 (GND), U3.20 (GND)
unnamed: R5.1, S1.6 (K_R)
unnamed: R6.1, S1.8 (K_G)
unnamed: R7.1, S1.5 (K_B)
unnamed: R8.1, S2.6 (K_R)
unnamed: R9.1, S2.8 (K_G)
unnamed: R10.1, S2.5 (K_B)
unnamed: R11.1, S3.6 (K_R)
unnamed: R12.1, S3.8 (K_G)
unnamed: R13.1, S3.5 (K_B)
unnamed: R14.1, S4.6 (K_R)
unnamed: R15.1, S4.8 (K_G)
unnamed: R16.1, S4.5 (K_B)
unnamed: R17.2, SW1.A
unnamed: R18.2, SW1.B
unnamed: R20.1, U1.7 (~CLR)
unnamed: R21.1, U2.7 (~CLR)
PSFHCLK: R2.1, R2.2, U1.15 (SRCK), U2.15 (SRCK), U3.19 (PA3/ADC3/SCK1)
PSHFDATA: R1.1, R1.2, U1.2 (SERIN), U3.17 (PA1/ADC1/DO1)
PSHFDATA2: U1.9 (SEROUT), U2.2 (SERIN)
PSHFUDATE: U1.10 (RCK), U2.10 (RCK), U3.9 (PB2)
S1_G: R6.2, U1.5 (DARIN2)
S1_R: R5.2, U1.4 (DRAIN1)
S1_b: R7.2, U1.3 (DRAIN0)
S2_B: R10.2, U1.12 (DARIN5)
S2_G: R9.2, U1.14 (DRAIN7)
S2_R: R8.2, U1.13 (DRAIN6)
S3_B: R13.2, U2.3 (DRAIN0)
S3_G: R12.2, U2.5 (DARIN2)
S3_R: R11.2, U2.4 (DRAIN1)
S4_B: R16.2, U2.12 (DARIN5)
S4_G: R15.2, U2.14 (DRAIN7)
S4_R: R14.2, U2.13 (DRAIN6)
SCL: J1.4, J2.4, U3.11 (PB0/ADC11/SCL)
SDA: J1.3, J2.3, U3.10 (PB1/ADC10/SDA)
UPDI: J5.2, U3.16 (PA0/UPDI/RESET)
UPDI_w: J1.2, J2.2, J4.2, J5.1
VCC: C3.1, C4.1, J3.5, J5.4, R20.2, R21.2, S1.7 (Anode), S2.7 (Anode), S3.7 (Anode), S4.7 (Anode), U1.1 (VCC), U2.1 (VCC)
VCC_w: C5.1, C6.2, J1.1, J2.1, J4.3, J5.3, U3.1 (VCC)

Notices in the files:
a3mix/a3mix_mainboard_v02/a3mix.kicad_pcb:
Licensed under CERN-OHL-S v2
